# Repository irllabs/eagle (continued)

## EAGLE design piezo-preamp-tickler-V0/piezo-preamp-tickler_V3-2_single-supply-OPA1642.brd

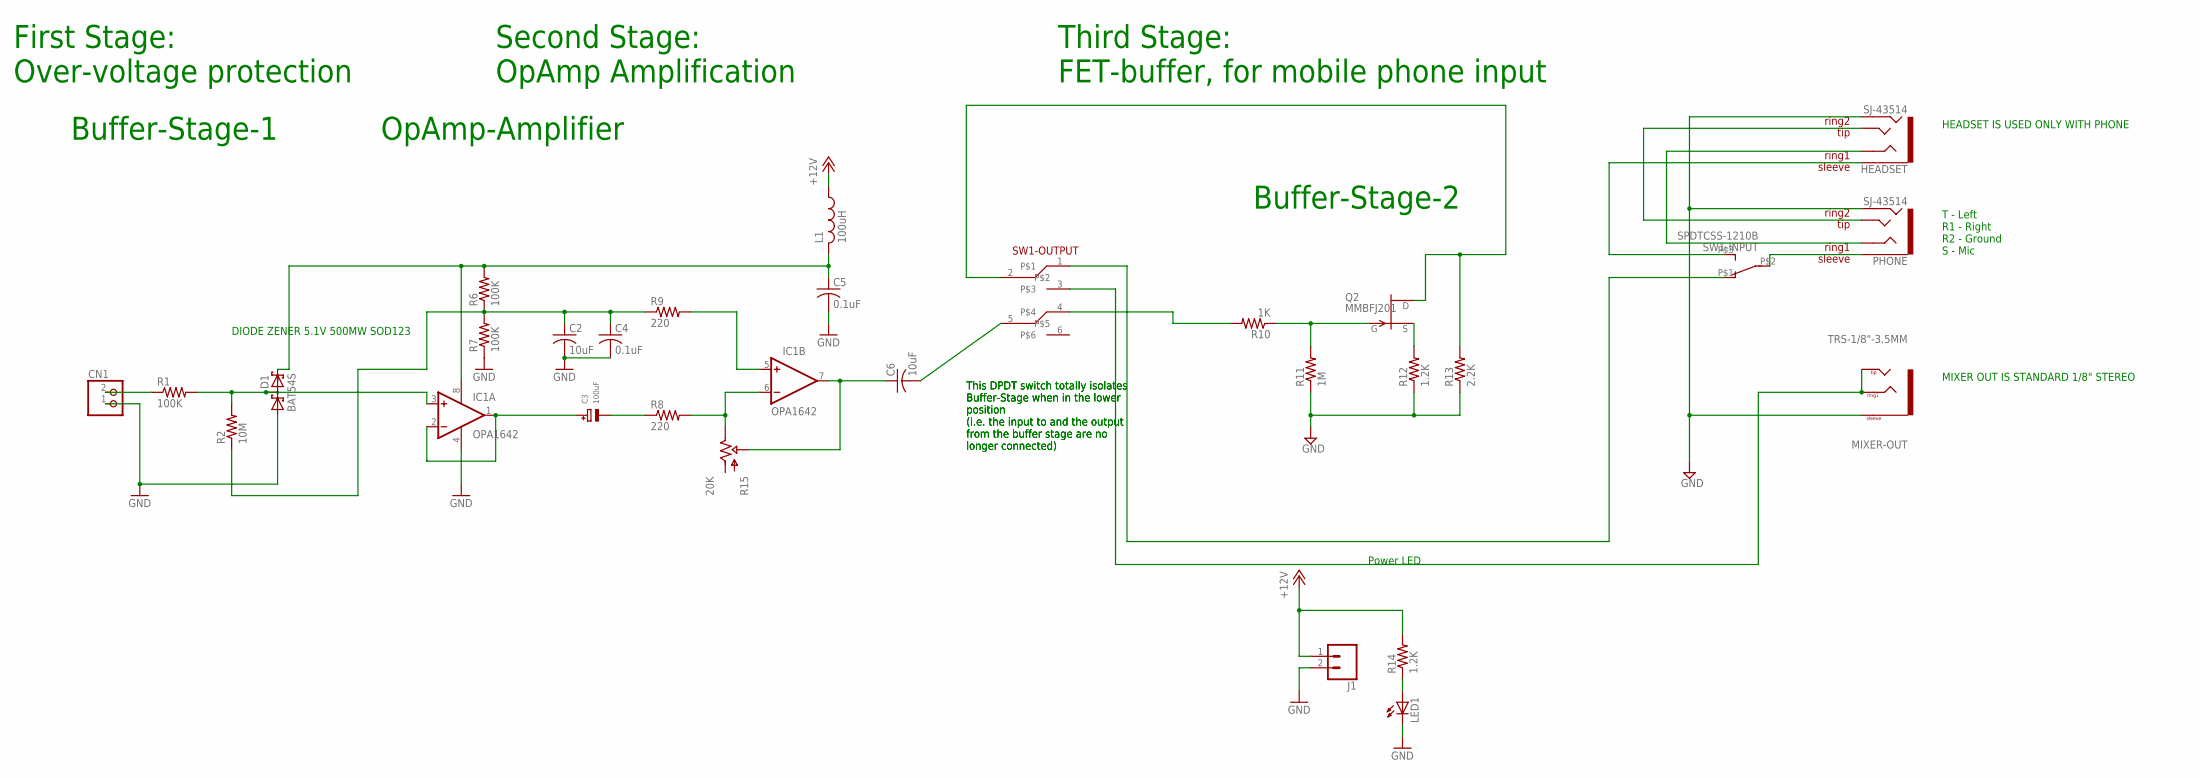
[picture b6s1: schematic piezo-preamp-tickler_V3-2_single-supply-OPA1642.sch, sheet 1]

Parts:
C2, C6: 10uF; C1206
C3: 100uF; EIA7343-31/D-R
C4, C5: 0.1uF; C0805K
CN1: JST_2PIN-THM; JST-PH-2-THM
D1: BAT54S; SOT23
HEADSET: SJ-43514; TRRS_SJ-43514-SMT-TR
IC1: OPA1642; SO08
J1: CONN_02LOCK; 1X02_LOCK
L1: 100uH; L3225P
LED1: LED3MM
MIXER-OUT: TRS-1/8"-3.5MM; TRS_SJ-3524-SMT
PHONE: SJ-43514; TRRS_SJ-43514-SMT-TR
Q2: MMBFJ201; SOT23
R1, R6, R7: 100K; R0603
R2: 10M; R0603
R8, R9: 220; R0603
R10: 1K; R0603
R11: 1M; R0603
R12, R14: 1.2K; R0603
R13: 2.2K; R0603
R15: 20K; TRIMPOT-MULTI
SW1-INPUT: SPDTCSS-1210B; SWITCH_SPDT_CSS-1210B
SW1-OUTPUT: SWITCH_DPDT; SWITCH_DPDT_CL-SB-22B

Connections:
+12V: J1.1, L1.1, R14.2; also elsewhere on the board
GATE2: Q2.3 (G), R10.1, R11.2
GND: C2.2, C4.2, C5.2, CN1.1 (2), D1.1 (A1), HEADSET.RING2, IC1.4 (V-), J1.2, LED1.K (C), MIXER-OUT.1 (SLEEVE), PHONE.RING2, R7.1, R11.1, R12.1, R13.1; also elsewhere on the board
unnamed: C3.+, IC1.1 (OUT), IC1.2 (-IN)
unnamed: R10.2, SW1-OUTPUT.4
unnamed: D1.3 (C1A2), IC1.3 (+IN), R1.2, R2.2
unnamed: Q2.2 (S), R12.2
unnamed: HEADSET.EARTH, SW1-INPUT.P$3 (3)
unnamed: SW1-INPUT.P$1 (1), SW1-OUTPUT.1
unnamed: MIXER-OUT.2 (TIP), MIXER-OUT.3 (RING1), MIXER-OUT.4 (TIP), SW1-OUTPUT.3
unnamed: IC1.5 (+IN), R9.2
unnamed: IC1.6 (-IN), R8.2, R15.P$1 (OUT), R15.P$3 (OUT), R15.P$4 (OUT), R15.P$6 (OUT), R15.P$9 (OUT)
unnamed: C6.2, SW1-OUTPUT.5
unnamed: CN1.2 (1), R1.1
unnamed: C6.1, IC1.7 (OUT), R15.P$10 (WIPER), R15.P$12 (WIPER), R15.P$13 (WIPER), R15.P$15 (WIPER), R15.P$16 (WIPER), R15.P$18 (WIPER)
unnamed: C5.1, D1.2 (C2), IC1.8 (V+), L1.2, R6.2
unnamed: C2.1, C4.1, R2.1, R6.1, R7.2, R9.1
unnamed: HEADSET.TIP, PHONE.TIP
unnamed: HEADSET.RING1, PHONE.RING1
unnamed: PHONE.EARTH, SW1-INPUT.P$2 (2)
unnamed: C3.-, R8.1
NAME: Q2.1 (D), R13.2, SW1-OUTPUT.2
unnamed: LED1.A, R14.1

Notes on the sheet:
Buffer-Stage-1
OpAmp-Amplifier
Buffer-Stage-2
Power LED
T - Left R1 - Right R2 - Ground S - Mic
This DPDT switch totally isolates Buffer-Stage when in the lower position (i.e. the input to and the output from the buffer stage are no longer connected)
HEADSET IS USED ONLY WITH PHONE
MIXER OUT IS STANDARD 1/8" STEREO
DIODE ZENER 5.1V 500MW SOD123
First Stage: Over-voltage protection
Second Stage: OpAmp Amplification
Third Stage: FET-buffer, for mobile phone input

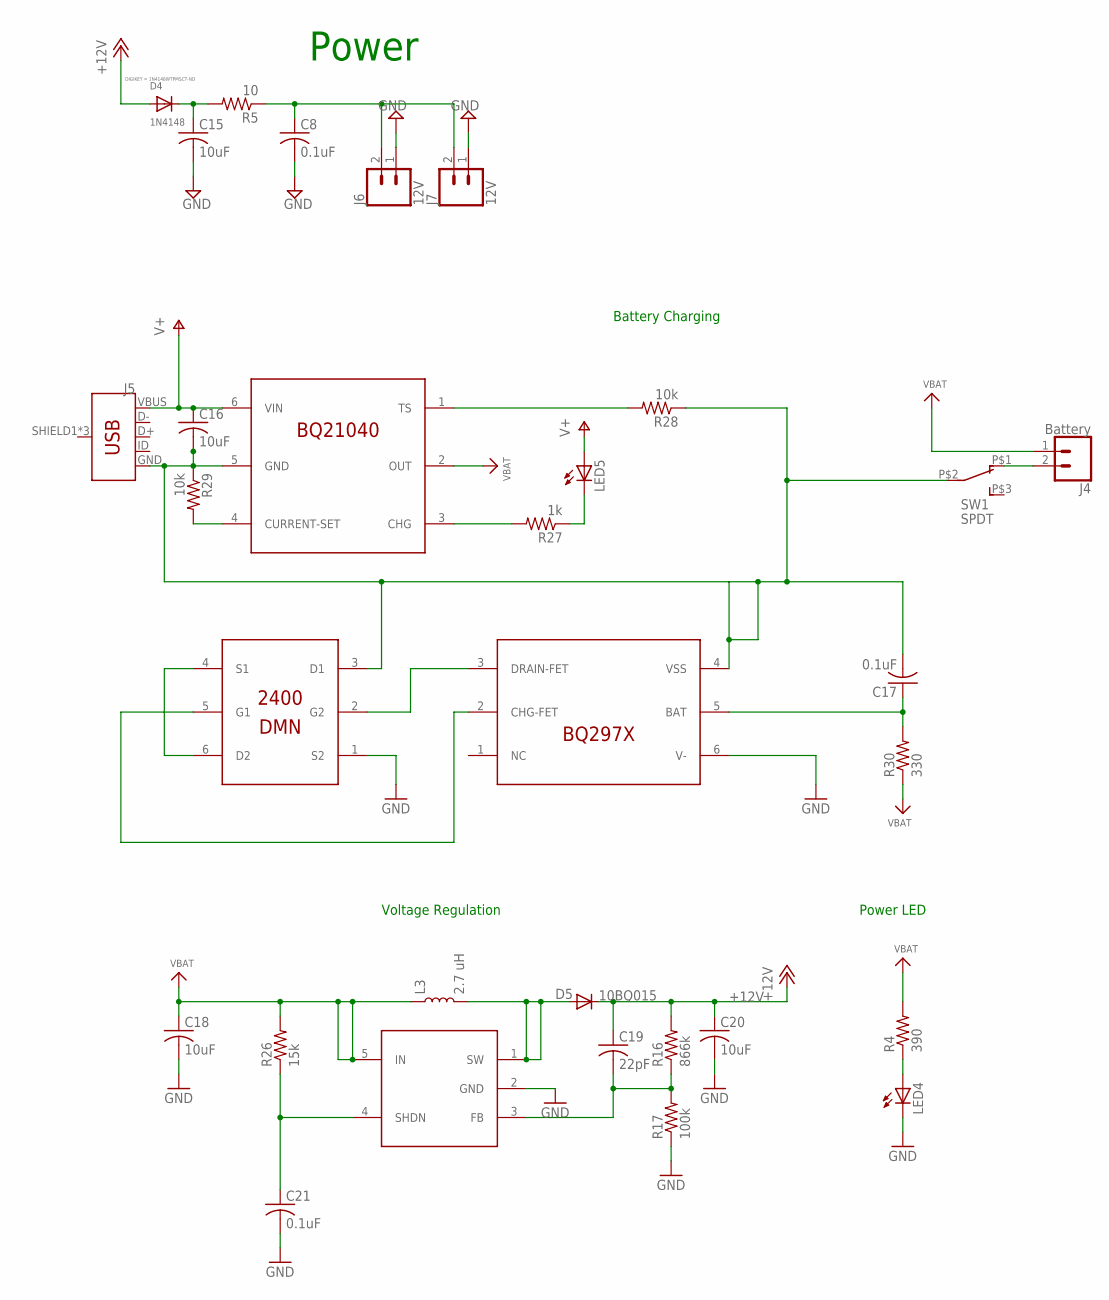
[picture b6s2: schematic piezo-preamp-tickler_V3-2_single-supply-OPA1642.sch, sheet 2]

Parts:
C8, C17, C21: 0.1uF; C0805K
C15, C16, C18, C20: 10uF; C0805K
C19: 22pF; C0805K
D4: 1N4148; SOD-123; DIGIKEY 1N4148WTPMSCT-ND
D5: 10BQ015; SMA-DIODE
J4: Battery; 1X02_LOCK
J5: USB_MICRO-BREDUCED_PASTE; USB-B-MICRO-SMD_RED_PASTE
J6, J7: 12V; 1X02
L3: 2.7 uH; CR54
LED4, LED5: LED3MM
Q1: BQ21040; SOT23-6
Q7: BQ297X; WSON-6
Q8: DMN2400; SOT-563
Q9: SC4503; SOT23-5
R4: 390; R0805
R5: 10; R0805
R16: 866k; R0805
R17: 100k; R0805
R26: 15k; R0805
R27: 1k; R0805
R28, R29: 10k; R0805
R30: 330; R0805
SW1: SPDT; SWITCH_SPDT_CL-SB-12B

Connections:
+12V: C19.1, C20.1, D4.A, D5.C, R16.2; also elsewhere on the board
GND: C8.2, C15.2, C18.2, C20.2, C21.2, J6.1, J7.1, LED4.K (C), Q7.6 (V-), Q8.1 (S2), Q9.2 (GND), R17.1; also elsewhere on the board
GND2: C16.2, C17.2, J5.GND, Q1.5 (GND), Q7.4 (VSS), Q8.3 (D1), R28.1, R29.1, SW1.P$2 (2)
unnamed: LED4.A, R4.1
unnamed: J4.2, SW1.P$1 (1)
unnamed: D5.A, L3.P$2 (2), Q9.1 (SW)
unnamed: C21.1, Q9.4 (SHDN), R26.1
unnamed: C19.2, Q9.3 (FB), R16.1, R17.2
unnamed: LED5.K (C), R27.1
unnamed: Q1.3 (CHG), R27.2
unnamed: Q1.1 (TS), R28.2
unnamed: Q1.4 (CURRENT-SET), R29.2
unnamed: C17.1, Q7.5 (BAT), R30.2
unnamed: Q8.4 (S1), Q8.6 (D2)
unnamed: Q7.2 (CHG-FET), Q8.5 (G1)
unnamed: Q7.3 (DRAIN-FET), Q8.2 (G2)
unnamed: C15.1, D4.C, R5.2
unnamed: C8.1, J6.2, J7.2, R5.1
V+: C16.1, J5.VBUS, LED5.A, Q1.6 (VIN)
VBAT: C18.1, J4.1, L3.P$1 (1), Q1.2 (OUT), Q9.5 (IN), R4.2, R26.2, R30.1

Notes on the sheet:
Voltage Regulation
Battery Charging
Power LED
Power

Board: 2 copper layers, 60 parts (0 on the bottom side), 41 nets, no tracks yet.

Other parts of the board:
J2: 1X02_LOCK
LED2: LED3MM
R3: 1.2K; R0603

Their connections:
+12V: J2.1, R3.2; also elsewhere on the board
GND: J2.2, LED2.K; also elsewhere on the board
unnamed: LED2.A, R3.1

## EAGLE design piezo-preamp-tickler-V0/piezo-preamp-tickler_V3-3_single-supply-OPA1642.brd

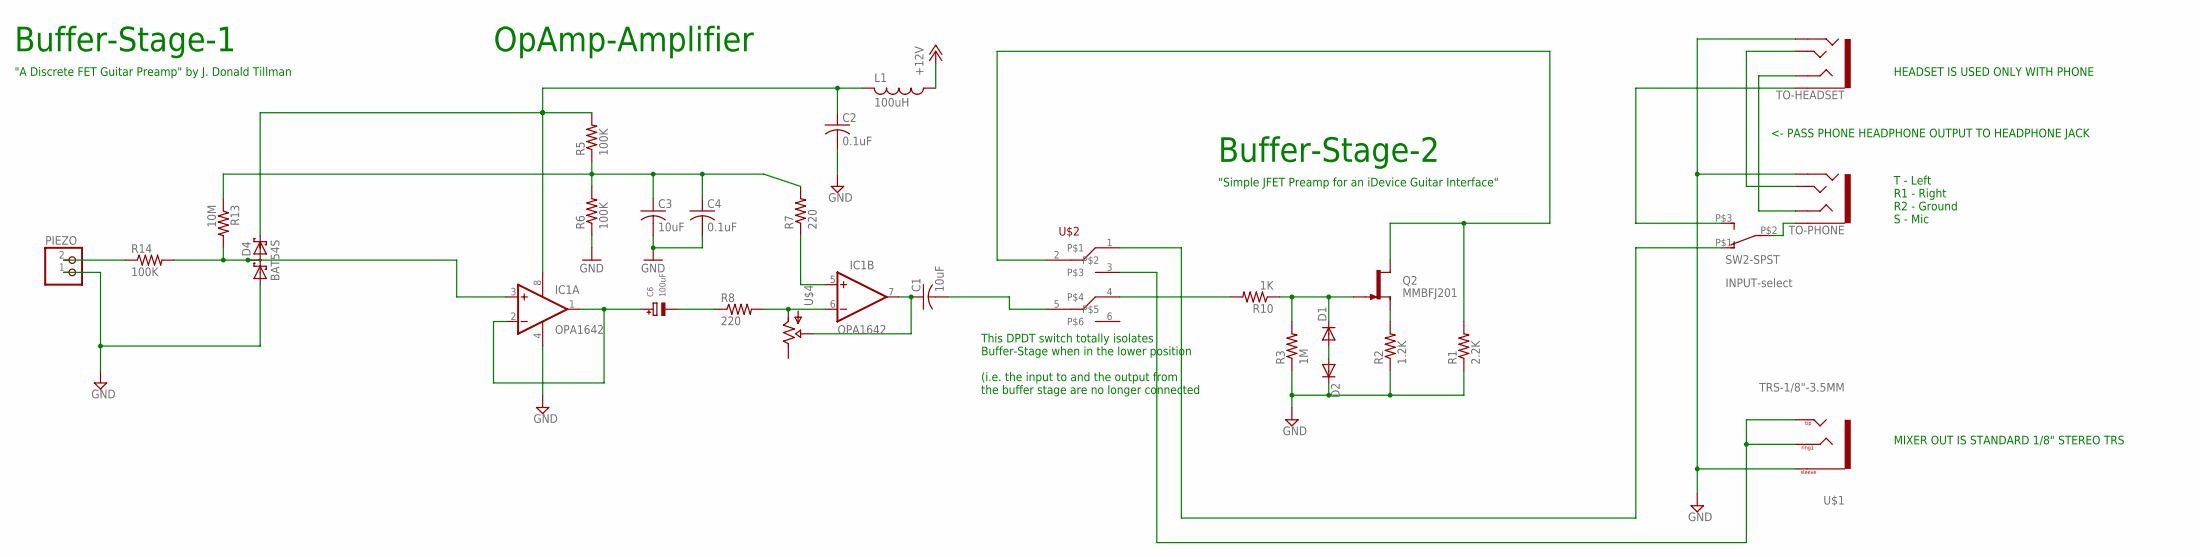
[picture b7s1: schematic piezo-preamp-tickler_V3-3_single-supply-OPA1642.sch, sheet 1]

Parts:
C1: 10uF; C0603
C2, C4: 0.1uF; C0805K
C3: 10uF; C0805K
C6: 100uF; EIA3216-18/A-R
D1, D2: DIODE-SOD123; SOD123
D4: BAT54S; SOT23
IC1: OPA1642; SO08
L1: 100uH; L3225P
PIEZO: JST_2PIN-THM; JST-PH-2-THM
Q2: MMBFJ201; SOT23-3
R1: 2.2K; R0603
R2: 1.2K; R0603
R3: 1M; R0603
R5, R6, R14: 100K; R0603
R7, R8: 220; R0603
R10: 1K; R0603
R13: 10M; R0603
SW2-SPST: INPUT-select; SWITCH_SPDT_CL-SB-12B
TO-HEADSET: AUDIO-JACK3LGPADS; AUDIO-JACK-TRRS-SMD
TO-PHONE: AUDIO-JACK3LGPADS; AUDIO-JACK-TRRS-SMD
U$1: TRS-1/8"-3.5MM; TRS_SJ-3524-SMT
U$2: SWITCH_DPDT; SWITCH_DPDT_CL-SB-22B
U$4: POTPOT-THUMB-ALPHA; POT-THUMB-14MM_ALPHA-RV100F-30-4K1B-B10K-B301

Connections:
+12V: L1.1; also elsewhere on the board
GND: C2.2, C3.2, C4.2, D2.C, D4.1 (A1), IC1.4 (V-), PIEZO.1 (2), R1.1, R2.1, R3.1, R6.1, TO-HEADSET.RING2, TO-PHONE.RING2, U$1.1 (SLEEVE); also elsewhere on the board
unnamed: D1.A, D2.A
unnamed: PIEZO.2 (1), R14.1
unnamed: Q2.2 (S), R2.2
unnamed: IC1.5 (+IN), R7.1
unnamed: C1.1, IC1.7 (OUT), U$4.P$3 (WIPER)
unnamed: IC1.6 (-IN), R8.2, U$4.P$1 (IN)
unnamed: D4.3 (C1A2), IC1.3 (+IN), R13.2, R14.2
unnamed: D1.C, Q2.3 (G), R3.2, R10.1
unnamed: R10.2, U$2.4
unnamed: U$1.2 (TIP), U$1.3 (RING1), U$1.4 (TIP), U$2.3
unnamed: TO-HEADSET.TIP, TO-PHONE.TIP
unnamed: C6.-, R8.1
unnamed: TO-HEADSET.RING1, TO-PHONE.RING1
unnamed: C1.2, U$2.5
unnamed: SW2-SPST.P$2 (2), TO-PHONE.EARTH
unnamed: SW2-SPST.P$1 (1), U$2.1
unnamed: C3.1, C4.1, R5.1, R6.2, R7.2, R13.1
unnamed: C6.+, IC1.1 (OUT), IC1.2 (-IN)
unnamed: C2.1, D4.2 (C2), IC1.8 (V+), L1.2, R5.2
SELECT: Q2.1 (D), R1.2, U$2.2

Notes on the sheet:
Buffer-Stage-1
OpAmp-Amplifier
Buffer-Stage-2
"A Discrete FET Guitar Preamp" by J. Donald Tillman
"Simple JFET Preamp for an iDevice Guitar Interface"
T - Left R1 - Right R2 - Ground S - Mic
HEADSET IS USED ONLY WITH PHONE
MIXER OUT IS STANDARD 1/8" STEREO TRS
<- PASS PHONE HEADPHONE OUTPUT TO HEADPHONE JACK
This DPDT switch totally isolates Buffer-Stage when in the lower position (i.e. the input to and the output from the buffer stage are no longer connected

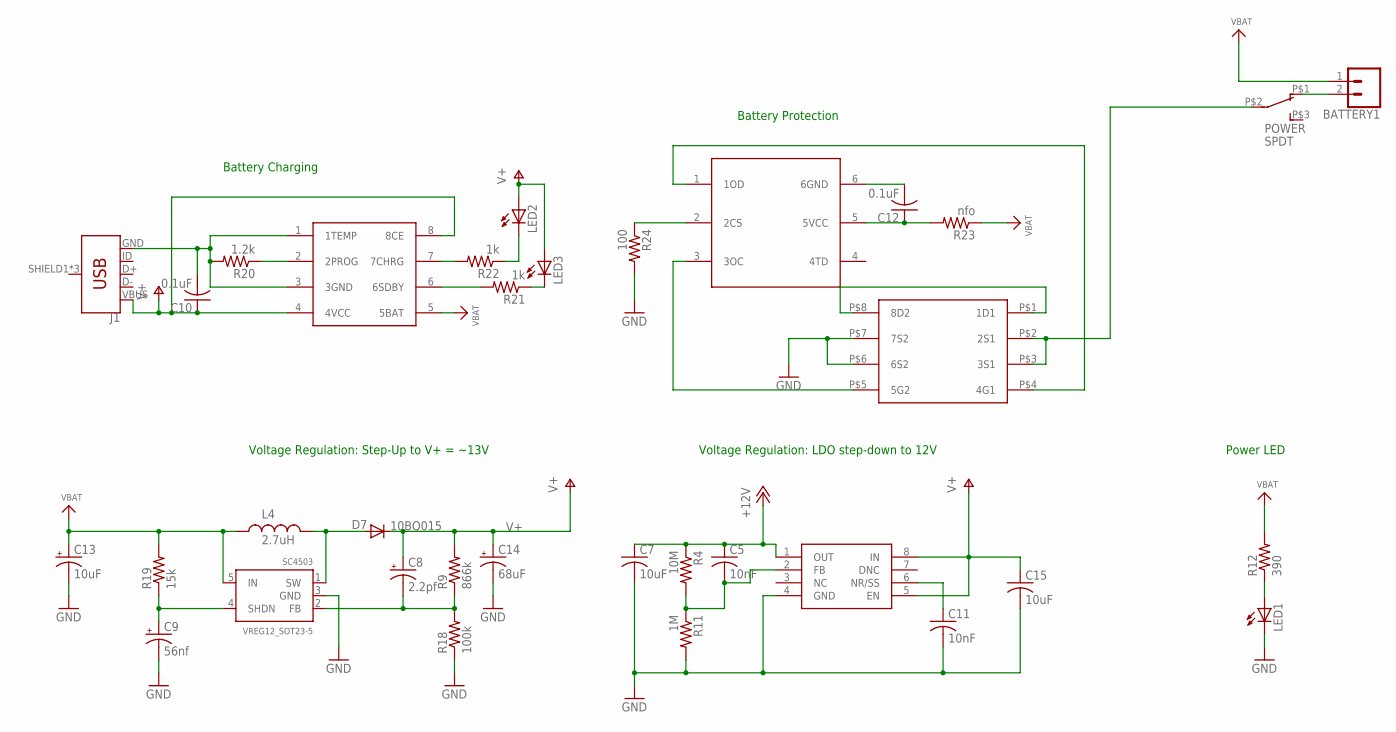
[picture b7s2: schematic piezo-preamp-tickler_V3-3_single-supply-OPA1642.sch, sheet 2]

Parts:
BATTERY1: CONN_02LOCK; 1X02_LOCK
C5, C11: 10nF; C0603
C7, C15: 10uF; C0603
C8: 2.2pf; EIA3216
C9: 56nf; EIA3528
C10, C12: 0.1uF; C0805K
C13: 10uF; EIA3216
C14: 68uF; EIA3528
D7: 10BQ015; SMA-DIODE
DW01A: DW01A; SOT23-6
F8205A: F8205A
J1: USB_MICRO-BREDUCED_PASTE; USB-B-MICRO-SMD_RED_PASTE
L4: 2.7uH; CR54
LED1, LED2, LED3: LED3MM
POWER: SPDT; SWITCH_SPDT_CL-SB-12B
R4: 10M; R0603
R9: 866k; R0603
R11: 1M; R0603
R12: 390; R0805
R18: 100k; R0603
R19: 15k; R0603
R20: 1.2k; R0603
R21, R22: 1k; R0603
R23: nfo; R0603
R24: 100; R0603
SC4503: VREG12_SOT23-5; SOT23-5
TP4056: TP4056-CHIP; SO08
U$5: TPS7A49; MSOP-8

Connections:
+12V: C5.1, C7.1, R4.1, U$5.1 (OUT); also elsewhere on the board
GND: C7.2, C9.C (-), C11.2, C13.C (-), C14.C (-), C15.2, F8205A.P$6 (6S2), F8205A.P$7 (7S2), LED1.K (C), R11.2, R18.1, R24.2, SC4503.3 (GND), U$5.4 (GND); also elsewhere on the board
unnamed: LED1.A, R12.1
unnamed: F8205A.P$2 (2S1), F8205A.P$3 (3S1), POWER.P$2 (2)
unnamed: BATTERY1.2, POWER.P$1 (1)
unnamed: C5.2, R4.2, R11.1, U$5.2 (FB)
unnamed: C11.1, U$5.6 (NR/SS)
unnamed: C9.A (+), R19.1, SC4503.4 (SHDN)
unnamed: C8.C (-), R9.1, R18.2, SC4503.2 (FB)
unnamed: D7.A, L4.P$2 (2), SC4503.1 (SW)
unnamed: C10.2, J1.GND, R20.2, TP4056.1 (1TEMP), TP4056.3 (3GND)
unnamed: DW01A.1 (1OD), F8205A.P$4 (4G1)
unnamed: R20.1, TP4056.2 (2PROG)
unnamed: DW01A.3 (3OC), F8205A.P$5 (5G2)
unnamed: R22.2, TP4056.7 (7CHRG)
unnamed: R21.2, TP4056.6 (6SDBY)
unnamed: LED3.K (C), R21.1
unnamed: LED2.K (C), R22.1
unnamed: C12.1, DW01A.5 (5VCC), R23.2
unnamed: C12.2, DW01A.6 (6GND)
unnamed: DW01A.2 (2CS), R24.1
unnamed: F8205A.P$1 (1D1), F8205A.P$8 (8D2)
V+: C8.A (+), C10.1, C14.A (+), C15.1, D7.C, J1.VBUS, LED2.A, LED3.A, R9.2, TP4056.4 (4VCC), TP4056.8 (8CE), U$5.5 (EN), U$5.8 (IN)
VBAT: BATTERY1.1, C13.A (+), L4.P$1 (1), R12.2, R19.2, R23.1, SC4503.5 (IN), TP4056.5 (5BAT)

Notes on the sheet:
Voltage Regulation: Step-Up to V+ = ~13V
Battery Charging
Power LED
Battery Protection
Voltage Regulation: LDO step-down to 12V

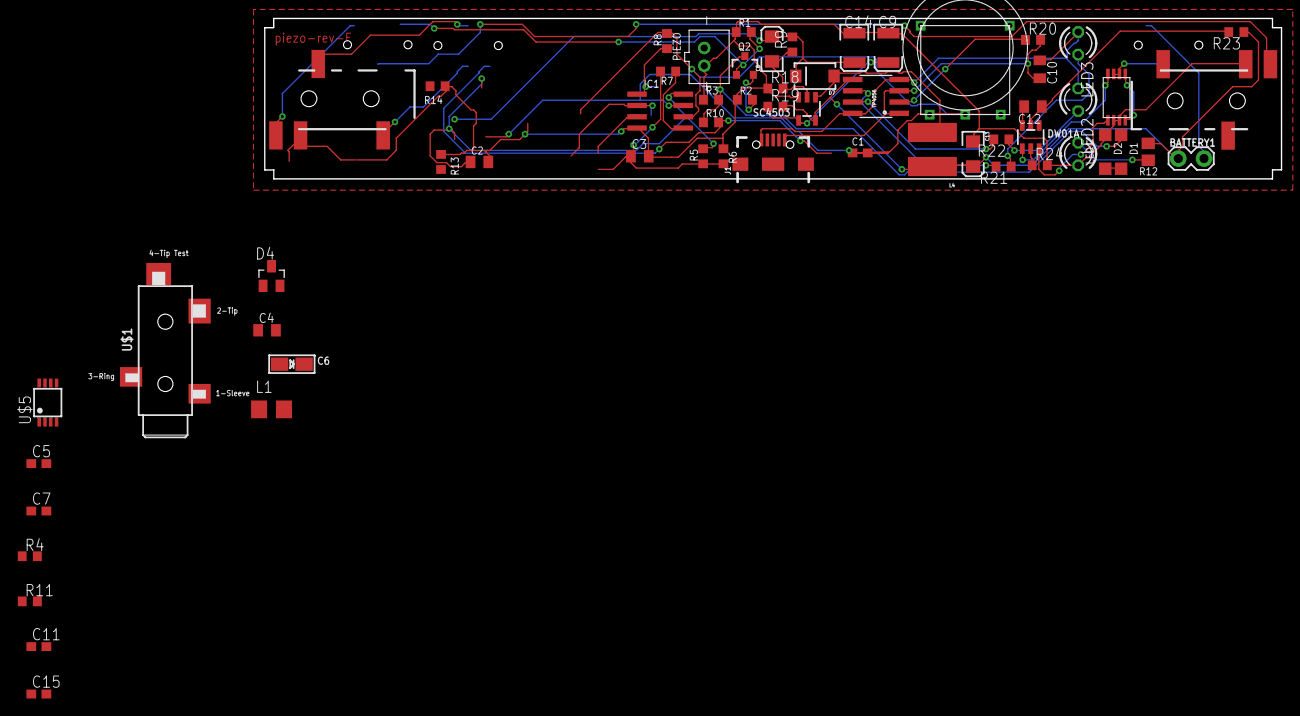
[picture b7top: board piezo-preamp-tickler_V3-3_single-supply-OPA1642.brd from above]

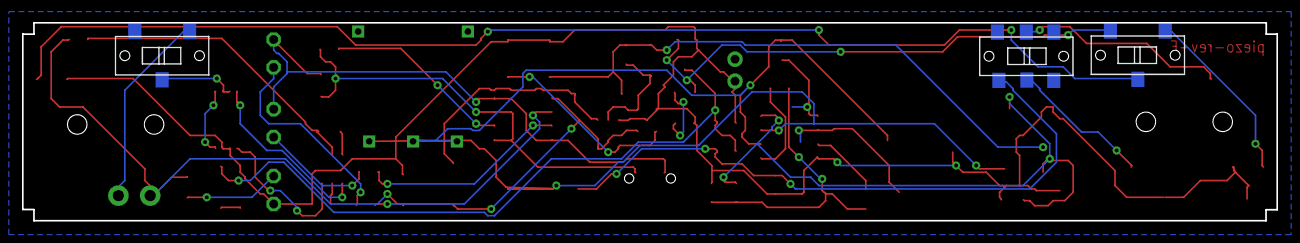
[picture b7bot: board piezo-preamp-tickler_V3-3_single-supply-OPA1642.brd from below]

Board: 2 copper layers, 114.3 x 18.0 mm, 62 parts (3 on the bottom side), 44 nets.
